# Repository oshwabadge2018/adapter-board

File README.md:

## Adapter board for USB-to-serial cable
adapter board to connect USB-to-serial cable to J1 header on Open Hardware Summit badge

### [OSH Park shared project](https://oshpark.com/shared_projects/39CXLX65)
Order the PCB from OSH Park:

[Adapter board for USB-to-serial cable](https://oshpark.com/shared_projects/39CXLX65)

### [Blog post](http://blog.oshpark.com/2018/10/19/adapter-board-for-open-hardware-summit-badge/)
[Adapter board for Open Hardware Summit badge](http://blog.oshpark.com/2018/10/19/adapter-board-for-open-hardware-summit-badge/)
> The badge features an ESP32 microcontroller running MicroPython firmware.  The firmware provides a Python interpreter prompt (REPL) on the serial port which allows interactive programming of the badge!

### Bill of Materials (BoM)
* **[Digi-Key shopping cart](https://www.digikey.com/short/jdb477)**

* Switch for programming mode
  * E-Switch EG1218
  * Slide Switch SPDT
  * Digi-Key: [EG1903-ND](https://www.digikey.com/short/jdmjh3)

* Pushbutton for reset
  * Omron B3F-1000
  * Tactile Switch SPST-NO
  * Digi-Key: [SW400-ND](https://www.digikey.com/short/jdmjhz)

* Header for FTDI usb-to-serial cable
  * TE AMP 9-146282-0-06
  * 1x6 Pin Header 0.1" pitch
  * Digi-Key: [A34253-06-ND](https://www.digikey.com/short/jdmjhd)

* Header to connect J1 socket on badge
  * Harwin M20-9720345
  * 2x3 Pin Header 0.1" pitch
  * Digi-Key: [952-1921-ND](https://www.digikey.com/short/jdmj9p)
  
* J1 header socket on the badge
  * Harwin 952-1781-ND
  * 2x3 Header Socket  0.1" pitch
  * Digi-Key: [M20-7830346](https://www.digikey.com/short/jdbtfc)

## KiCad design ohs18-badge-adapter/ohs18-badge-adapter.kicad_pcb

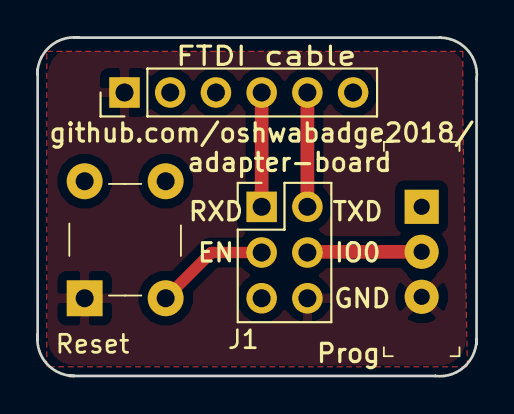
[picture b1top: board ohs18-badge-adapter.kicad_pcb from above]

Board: 2 copper layers, 24.4 x 18.8 mm, 4 parts (0 on the bottom side), 5 nets.

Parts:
J1: OHS18 Badge; PinHeader_2x03_P2.54mm_Vertical
J2: FTDI 3.3V USB to Serial; PinHeader_1x06_P2.54mm_Vertical
Mode1: EG1218; Switch_Slide_11.6x4mm_EG1218
Reset: B3F-1000; Switch_Tactile_THT_B3F-1xxx

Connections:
EN: J1.3, Reset.3
GND: J1.6, J2.1, Mode1.3, Reset.1
IO0: J1.4, Mode1.2
RXD: J1.2, J2.5
TXD: J1.1, J2.4

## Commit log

2018-10-07 initial schematic
2018-10-07 finish layout of rev 1
2018-10-20 add images
